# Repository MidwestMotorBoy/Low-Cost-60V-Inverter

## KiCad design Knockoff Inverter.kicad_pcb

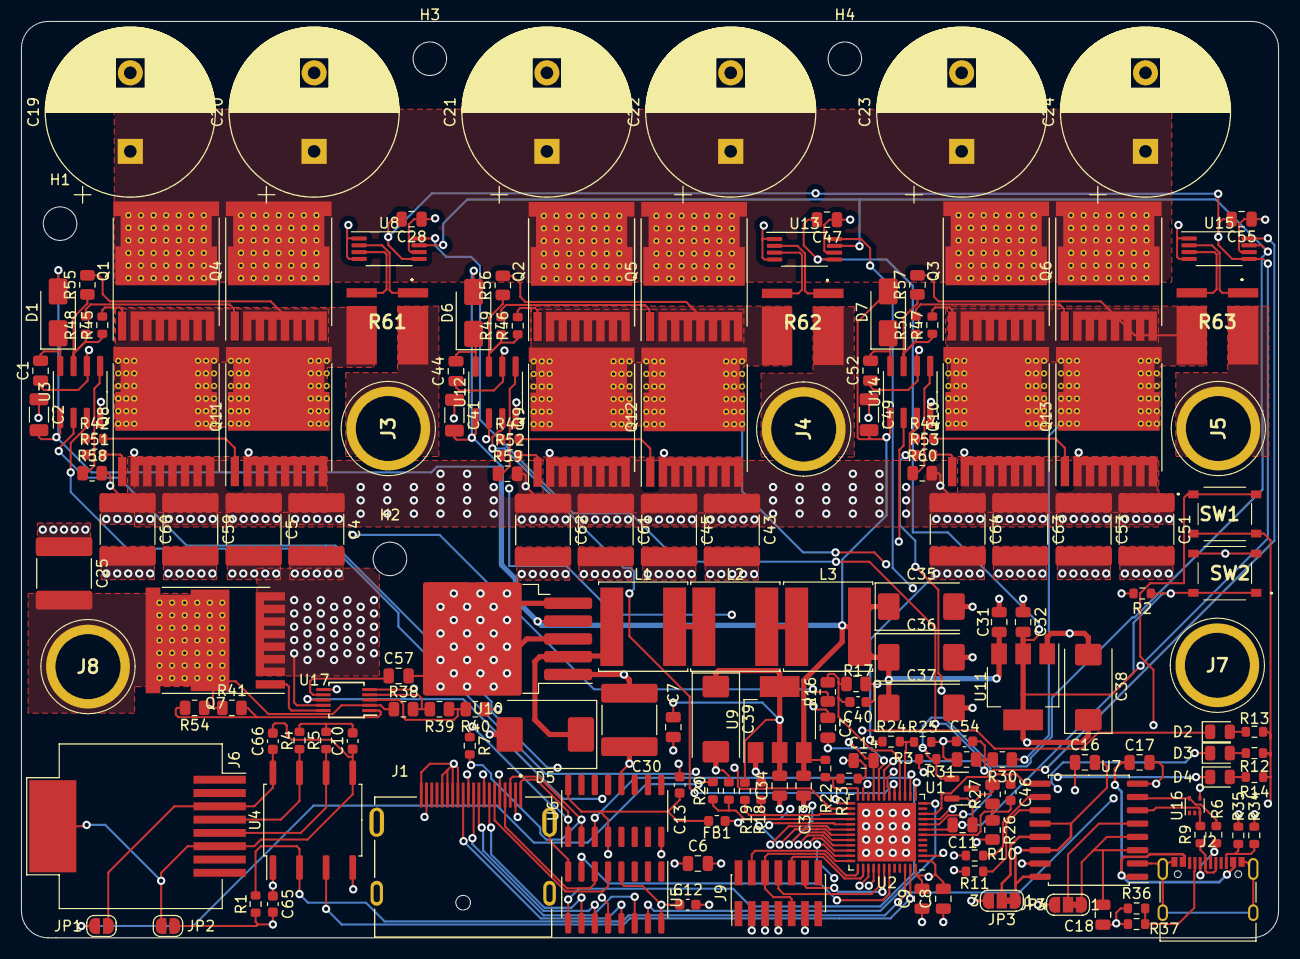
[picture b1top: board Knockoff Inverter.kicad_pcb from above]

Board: 4 copper layers, 120.0 x 87.5 mm, 176 parts (0 on the bottom side), 113 nets.

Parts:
C1, C3, C6, C7, C8, C9, C11, C14, C16, C17, C18, C28, C31, C32, C33, C34, C44, C47, C52, C55, C57: 100nF-100V-10%-0805; C_0805_2012Metric
C2, C41, C49: 1uF-100V-10%-1206; C_1206_3216Metric
C4, C5, C25, C30, C43, C45, C51, C53, C59, C60, C61, C62, C63, C64: 10uF-100V-10%-2220; C_2220_5650Metric
C10, C40, C46, C54: 10nF-50V-10%-0603; C_0603_1608Metric
C12, C13, C65, C66: 0.1uF; C_0603_1608Metric
C19, C20, C21, C22, C23, C24: 560uF-100V-P7.5mm-D16mm; CP_Radial_D16.0mm_P7.50mm
C35, C36, C37, C38, C39: 47uF-16V-CASE_D; CP_EIA-7343-31_Kemet-D
D1, D6, D7: 100V-2A-214AC; D_SMA
D2: GREEN-0805; LED_0805_2012Metric
D3: YELLOW-0805; LED_0805_2012Metric
D4: RED-0805; LED_0805_2012Metric
D5: 60V-0.75V@3A-SMC; D_SMC
FB1: 600Ω@100MHz-25%-0603; L_0603_1608Metric
H1, H2, H3, H4, H5, H6: MountingHole; MountingHole_3.2mm_M3
J1: 47272-0001; MOLEX_47272-0001
J2: USB_C_Receptacle_USB2.0; USB_C_Receptacle_XKB_U262-16XN-4BVC11
J3, J4, J5, J7, J8: Screw_Terminal_01x01; 7466005R
J6: Conn_01x08; RJ45_Molex_0855135013_Vertical
J9: Conn_02x07_Odd_Even; PinHeader_2x07_P1.27mm_Vertical_SMD
JP1, JP2: SolderJumper_2_Open; SolderJumper-2_P1.3mm_Open_RoundedPad1.0x1.5mm
JP3, JP4: Jumper; SolderJumper-3_P1.3mm_Bridged12_RoundedPad1.0x1.5mm_NumberL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
L1, L2, L3: 100uH-1A-20%-8x8mm; L_Sunlord_SWPA8040S
Q1, Q2, Q3, Q4, Q5, Q6, Q7: HYG017N10NS1TA; Infineon_PG-HSOF-8-1_ThermalVias
Q8, Q9, Q10, Q11, Q12, Q13: HYG017N10NS1TA; Infineon_PG-HSOF-8-1_ThermalVias_GAPPED
R1, R2, R19, R20, R22, R24, R34, R35, R36, R37: 10kΩ-1%-0603; R_0603_1608Metric
R3: DNP 10kΩ-1%-0603; R_0603_1608Metric
R4, R5: 47Ω-1%-0603; R_0603_1608Metric
R6, R9, R10, R11: 27Ω-0603-1%; R_0603_1608Metric
R7, R12, R13, R14, R18, R21, R23, R25: 100Ω-1%-0603; R_0603_1608Metric
R16, R17, R26, R27, R30, R31, R54: 10kΩ-0805-0.1%; R_0805_2012Metric
R38, R55, R56, R57, R58, R59, R60: 100kΩ-0805-1%; R_0805_2012Metric
R39: 6.4kΩ-0805-0.1%; R_0805_2012Metric
R40: 3.6kΩ-0805-1%; R_0805_2012Metric
R41: 2x10kΩ-0805-0.1%; R_0805_2012Metric
R42, R43, R44, R45, R46, R47, R48, R49, R50, R51, R52, R53: 10Ω-0603-1%; R_0603_1608Metric
R61, R62, R63: 300uΩ-2726-1%; BVBMR00110
SW1, SW2: SW_DIP_x01; TS1187ABAB
U1: DNP LM4040DBZ-2.5; SOT-23
U2: STM32G431CBUx; QFN-48-1EP_7x7mm_P0.5mm_EP5.6x5.6mm
U3, U12, U14: IRS21867S; SOIC-8_3.9x4.9mm_P1.27mm
U4: ISO1050DUB; SOP-8_6.62x9.15mm_P2.54mm
U5: SN65LVDS31D; SOIC-16_3.9x9.9mm_P1.27mm
U6: SN65LVDS33D; SOIC-16_3.9x9.9mm_P1.27mm
U7: ADUM4160; SOIC-16W_7.5x10.3mm_P1.27mm
U8, U13, U15: CSA231MA; TSSOP-8_4.4x3mm_P0.65mm
U9: AMS1117-3.3; SOT-223-3_TabPin2
U10: LM2591HVS-12; TO-263-5_TabPin3
U11: AMS1117-5.0; SOT-223-3_TabPin2
U16: TPD2E2U06; SOT-553
U17: LM5060; MSOP-10_3x3mm_P0.5mm

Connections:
5V_ISO: C66.1, J6.3, JP1.2 (B), U4.8 (VCC2)
+3.3V: C6.2, C7.2, C8.2, C9.2, C12.1, C13.1, C16.2, C34.2, C39.1, C65.1, FB1.1, J1.13, J1.14, J1.15, J1.16, J1.20, J9.3, JP3.1 (A), R2.2, R3.1, R12.1, R13.1, R14.1, R19.1, SW1.2, U2.1 (VBAT), U2.23 (VDD), U2.35 (VDD), U2.48 (VDD), U4.1 (VCC1), U5.4 (G), U5.16 (VCC), U6.4 (G), U6.16 (VCC), U7.12 (PIN), U7.14 (VDD2), U7.16 (VBUS2), U9.2 (VO)
+5V: C28.2, C32.2, C38.1, C47.2, C55.2, JP1.1 (A), R20.1, U8.5 (V+), U11.2 (VO), U13.5 (V+), U15.5 (V+)
+12V: C2.2, C31.2, C33.2, C35.1, C36.1, C37.1, C41.2, C49.2, D1.2 (A), D6.2 (A), D7.2 (A), L3.2, R22.1, U3.1 (VCC), U9.3 (VI), U10.4 (FB), U11.3 (VI), U12.1 (VCC), U14.1 (VCC)
/CAN/CAN_TX: U2.47 (PB9), U4.3 (TXD)
/DC INPUT/EN: U2.25 (PB12), U17.5 (EN)
/DC INPUT/nPGD: U2.26 (PB13), U17.8 (~PGD)
/MCU/ADC1_IN1: U2.8 (PA0), U8.8
/MCU/ADC1_IN2: U2.9 (PA1), U13.8
/MCU/ADC1_IN3: U2.10 (PA2), U15.8
/MCU/ADC2_IN4: R24.2, R25.1, U2.15 (PA7)
/MCU/ADC2_IN5: C40.2, R16.2, R17.1, U2.16 (PC4)
/MCU/ADC2_IN10: C46.2, R26.2, R27.1, U2.6 (PF1)
/MCU/ADC2_IN12: C54.2, R30.2, R31.1, U2.19 (PB2)
/MCU/ADC2_IN14: R22.2, R23.1, U2.24 (PB11)
/MCU/ADC2_IN15: R20.2, R21.1, U2.28 (PB15)
/MCU/OPAMP2_VINP: R18.1, R19.2, U2.27 (PB14)
/MCU/SPI1_MISO: U2.14 (PA6), U6.3 (1Y)
/MCU/SPI1_MOSI: U2.43 (PB5), U5.7 (2A)
/MCU/SPI1_NSS: U2.12 (PA4), U5.15 (4A)
/MCU/SPI1_SCK: U2.13 (PA5), U5.9 (3A)
/MCU/TIM_CH1: U2.30 (PA8), U3.2 (HIN)
/MCU/TIM_CH1N: U2.2 (PC13), U3.3 (LIN)
/MCU/TIM_CH2: U2.31 (PA9), U12.2 (HIN)
/MCU/TIM_CH2N: U2.17 (PB0), U12.3 (LIN)
/MCU/TIM_CH3: U2.32 (PA10), U14.2 (HIN)
/MCU/TIM_CH3N: U2.18 (PB1), U14.3 (LIN)
/MCU/USB_DM: R11.1, U2.33 (PA11)
/MCU/USB_DP: R10.2, U2.34 (PA12)
CAN_IN+: J6.4, R4.1, U4.7 (CANH)
CAN_IN-: J6.5, R5.2, U4.6 (CANL)
CAN_RX: R1.1, SW1.1, U2.46 (PB8), U4.2 (RXD)
GND: C2.1, C3.1, C4.1, C5.1, C6.1, C7.1, C8.1, C9.1, C11.1, C12.2, C13.2, C14.1, C16.1, C19.2, C20.2, C21.2, C22.2, C23.2, C24.2, C25.1, C28.1, C30.1, C31.1, C32.1, C33.1, C34.1, C35.2, C36.2, C37.2, C38.2, C39.2, C40.1, C41.1, C43.1, C45.1, C46.1, C47.1, C49.1, C51.1, C53.1, C54.1, C55.1, C57.2, C59.1, C60.1, C61.1, C62.1, C63.1, C64.1, C65.2, D5.2 (A), J1.2, J1.5, J1.8, J1.11, J1.19, J1.S1 (SHIELD), J1.S2 (SHIELD), J1.S3 (SHIELD), J1.S4 (SHIELD), J7.1, J9.5, J9.7, J9.11, JP2.1 (A), JP3.3 (B), Q8.2 (S), Q9.2 (S), Q10.2 (S), Q11.2 (S), Q12.2 (S), Q13.2 (S), R1.2, R17.2, R18.2, R21.2, R23.2, R25.2, R27.2, R31.2, R40.2, R58.2, R59.2, R60.2, SW2.2, U1.2 (A), U2.49 (VSS), U3.4 (COM), U4.4 (GND1), U5.8 (GND), U5.12 (~G), U6.8 (GND), U6.12 (~G), U7.9 (GND2), U7.15 (GND2), U8.1 (GND), U8.4 (GND), U8.6 (REF2), U9.1 (GND), U10.3 (GND), U10.5 (~ON/OFF), U11.1 (GND), U12.4 (COM), U13.1 (GND), U13.4 (GND), U13.6 (REF2), U14.4 (COM), U15.1 (GND), U15.4 (GND), U15.6 (REF2), U17.6 (GND)
GND1: C17.1, C18.1, J2.A1 (GND), J2.A12 (GND), J2.B1 (GND), J2.B12 (GND), J2.S1 (SHIELD), JP4.3 (B), R34.1, R35.1, R36.1, R37.1, U7.2 (GND1), U7.8 (GND1), U16.4
GND_ISO: C10.1, C66.2, J6.6, J6.9, JP2.2 (B), U4.5 (GND2)
JTDI: J9.10, U2.38 (PA15)
JTRST: J9.12, U2.42 (PB4)
NSRST: C11.2, R2.1, SW2.1, U2.7 (PG10)
unnamed: C10.2, R4.2, R5.1
unnamed: C1.2, D1.1 (K), U3.8 (VB)
unnamed: D2.2 (A), R13.2
unnamed: D2.1 (K), U2.29 (PC6)
unnamed: D3.2 (A), R12.2
unnamed: D3.1 (K), U2.39 (PC10)
unnamed: D4.2 (A), R14.2
unnamed: D4.1 (K), U2.40 (PC11)
unnamed: D5.1 (K), L1.1, U10.2 (OUT)
unnamed: C44.2, D6.1 (K), U12.8 (VB)
unnamed: C52.2, D7.1 (K), U14.8 (VB)
unnamed: J2.A5 (CC1), R36.2, R37.2
unnamed: J2.B5 (CC2), R34.2, R35.2
unnamed: J2.A6 (D+), J2.B6 (D+), R9.2
unnamed: J2.A7 (D-), J2.B7 (D-), R6.1
unnamed: J3.1, R61.1
unnamed: J4.1, R62.1
unnamed: J5.1, R63.1
unnamed: C25.2, J8.1, Q7.3 (D), R38.1, R41.1, R54.1, U17.2 (VIN)
unnamed: JP3.2 (C), U7.13 (SPD)
unnamed: C18.2, JP4.1 (A), U7.3 (VDD1), U7.4 (PDEN)
unnamed: JP4.2 (C), U7.5 (SPU)
unnamed: L1.2, L2.1
unnamed: L2.2, L3.1
unnamed: Q1.1 (G), R45.2
unnamed: C1.1, Q1.2 (S), Q4.2 (S), Q8.3 (D), Q11.3 (D), R16.1, R55.2, R61.4, U3.6 (VS)
unnamed: Q2.1 (G), R46.2
unnamed: Q3.1 (G), R47.2
unnamed: Q4.1 (G), R48.2
unnamed: Q5.1 (G), R49.2
unnamed: Q6.1 (G), R50.2
unnamed: Q7.1 (G), U17.10 (GATE)
unnamed: Q8.1 (G), R51.2
unnamed: Q9.1 (G), R52.2
unnamed: C52.1, Q3.2 (S), Q6.2 (S), Q10.3 (D), Q13.3 (D), R30.1, R57.2, R63.4, U14.6 (VS)
unnamed: Q10.1 (G), R53.2
unnamed: Q11.1 (G), R42.2
unnamed: C44.1, Q2.2 (S), Q5.2 (S), Q9.3 (D), Q12.3 (D), R26.1, R56.2, R62.4, U12.6 (VS)
unnamed: Q12.1 (G), R43.2
unnamed: Q13.1 (G), R44.2
unnamed: C14.2, FB1.2, U2.21 (VDDA)
unnamed: R45.1, R48.1, R55.1, U3.7 (HO)
unnamed: R42.1, R51.1, R58.1, U3.5 (LO)
unnamed: R10.1, U7.10 (DD+)
unnamed: R11.2, U7.11 (DD-)
unnamed: R6.2, U7.7 (UD+), U16.5
unnamed: R9.1, U7.6 (UD-), U16.3
unnamed: C17.2, J2.A4 (VBUS), J2.A9 (VBUS), J2.B4 (VBUS), J2.B9 (VBUS), U7.1 (VBUS1)
unnamed: R61.2, U8.2 (+)
unnamed: R61.3, U8.3 (-)
unnamed: R46.1, R49.1, R56.1, U12.7 (HO)
unnamed: R43.1, R52.1, R59.1, U12.5 (LO)
unnamed: R62.2, U13.2 (+)
unnamed: R62.3, U13.3 (-)
unnamed: R47.1, R50.1, R57.1, U14.7 (HO)
unnamed: R44.1, R53.1, R60.1, U14.5 (LO)
unnamed: R63.2, U15.2 (+)
unnamed: R63.3, U15.3 (-)
unnamed: R39.2, R40.1, U17.3 (OVP)
unnamed: R41.2, R54.2, U17.1 (SENSE)
unnamed: C57.1, U17.7 (TIMER)
unnamed: R38.2, R39.1, U17.4 (UVLO)
SPI_MISO_+: J1.1, R7.1, U6.1 (1B)
SPI_MISO_-: J1.3, R7.2, U6.2 (1A)
SPI_MOSI_+: J1.4, U5.6 (2Y)
SPI_MOSI_-: J1.6, U5.5 (2Z)
SPI_SCK_+: J1.7, U5.10 (3Y)
SPI_SCK_-: J1.9, U5.11 (3Z)
SPI_nSS_+: J1.10, U5.14 (4Y)
SPI_nSS_-: J1.12, U5.13 (4Z)
SWCLK: J9.6, J9.9, U2.37 (PA14)
SWDIO: J9.4, U2.36 (PA13)
SWO: J9.8, U2.41 (PB3)
VBUS: C4.2, C5.2, C19.1, C20.1, C21.1, C22.1, C23.1, C24.1, C30.2, C43.2, C45.2, C51.2, C53.2, C59.2, C60.2, C61.2, C62.2, C63.2, C64.2, Q1.3 (D), Q2.3 (D), Q3.3 (D), Q4.3 (D), Q5.3 (D), Q6.3 (D), Q7.2 (S), R24.1, U10.1 (VIN), U17.9 (OUT)
VREF_OUT: C3.2, R3.2, U1.1 (K), U2.20 (VREF+), U8.7 (REF1), U13.7 (REF1), U15.7 (REF1)

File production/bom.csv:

Value,Designator,Footprint,LCSC Part #
100nF-100V-10%-0805,"C1, C11, C14, C16, C17, C18, C28, C3, C31, C32, C33, C34, C44, C47, C52, C55, C57, C6, C7, C8, C9",805,C28233
10nF-50V-10%-0603,"C10, C40, C46, C54",603,C57112
0.1uF,"C12, C13, C65, C66",603,C14663
560uF-100V-P7.5mm-D16mm,"C19, C20, C21, C22, C23, C24",CP_Radial_D16.0mm_P7.50mm,
1uF-100V-10%-1206,"C2, C41, C49",1206,C13832
10uF-100V-10%-2220,"C25, C30, C4, C43, C45, C5, C51, C53, C59, C60, C61, C62, C63, C64",2220,C2843466
47uF-16V-CASE_D,"C35, C36, C37, C38, C39",CP_EIA-7343-31_Kemet-D,C7227
100V-2A-214AC,"D1, D6, D7",D_SMA,C14996
GREEN-0805,D2,805,C2297
YELLOW-0805,D3,805,C2296
RED-0805,D4,805,C84256
60V-0.75V@3A-SMC,D5,D_SMC,C35722
600Ω@100MHz-25%-0603,FB1,603,C1002
MountingHole,"H1, H2, H3, H4",MountingHole_3.2mm_M3,
47272-0001,J1,MOLEX_47272-0001,C711350
USB_C_Receptacle_USB2.0,J2,USB_C_Receptacle_XKB_U262-16XN-4BVC11,C319148
Screw_Terminal_01x01,"J3, J4, J5, J7, J8",7466005R,
Conn_01x08,J6,RJ45_Molex_0855135013_Vertical,
Conn_02x07_Odd_Even,J9,PinHeader_2x07_P1.27mm_Vertical_SMD,C2881912
SolderJumper_2_Open,"JP1, JP2",SolderJumper-2_P1.3mm_Open_RoundedPad1.0x1.5mm,
Jumper,"JP3, JP4",SolderJumper-3_P1.3mm_Bridged12_RoundedPad1.0x1.5mm_NumberLabels,
100uH-1A-20%-8x8mm,"L1, L2, L3",L_Sunlord_SWPA8040S,C83468
HYG017N10NS1TA,"Q1, Q2, Q3, Q4, Q5, Q6, Q7",Infineon_PG-HSOF-8-1_ThermalVias,C5205219
HYG017N10NS1TA,"Q10, Q11, Q12, Q13, Q8, Q9",Infineon_PG-HSOF-8-1_ThermalVias_GAPPED,C5205219
10kΩ-1%-0603,"R1, R19, R2, R20, R22, R24, R34, R35, R36, R37",603,C25197
27Ω-0603-1%,"R10, R11, R6, R9",603,C25190
100Ω-1%-0603,"R12, R13, R14, R18, R21, R23, R25, R7",603,C22775
10kΩ-0805-0.1%,"R16, R17, R26, R27, R30, R31, R54",805,C5159707
DNP 10kΩ-1%-0603,R3,603,
100kΩ-0805-1%,"R38, R55, R56, R57, R58, R59, R60",805,C149504
6.4kΩ-0805-0.1%,R39,805,C865510
47Ω-1%-0603,"R4, R5",603,C23182
3.6kΩ-0805-1%,R40,805,C351568
2x10kΩ-0805-0.1%,R41,805,C5159707
10Ω-0603-1%,"R42, R43, R44, R45, R46, R47, R48, R49, R50, R51, R52, R53",603,C22859
300uΩ-2726-1%,"R61, R62, R63",BVBMR00110,C481539
SW_DIP_x01,"SW1, SW2",TS1187ABAB,C318884
DNP LM4040DBZ-2.5 ,U1,SOT-23,
LM2591HVS-12,U10,TO-263-5_TabPin3,C434500
AMS1117-5.0,U11,SOT-223-3_TabPin2,C6187
IRS21867S,"U12, U14, U3",SOIC-8_3.9x4.9mm_P1.27mm,C7432820
CSA231MA,"U13, U15, U8",TSSOP-8_4.4x3mm_P0.65mm,C5359409
TPD2E2U06,U16,SOT-553,C1972959
LM5060,U17,MSOP-10_3x3mm_P0.5mm,C2676940
STM32G431CBUx,U2,QFN-48-1EP_7x7mm_P0.5mm_EP5.6x5.6mm,C529356
ISO1050DUB,U4,SOP-8_6.62x9.15mm_P2.54mm,C16428
SN65LVDS31D,U5,SOIC-16_3.9x9.9mm_P1.27mm,C1508988
SN65LVDS33D,U6,SOIC-16_3.9x9.9mm_P1.27mm,C1508989
ADUM4160,U7,SOIC-16W_7.5x10.3mm_P1.27mm,C57791
AMS1117-3.3,U9,SOT-223-3_TabPin2,C6186

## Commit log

2023-07-16 Intial Push
    Going to redo routing with NS EW method
2023-07-17 Done with first pass, switching current amp due to stocking issues
